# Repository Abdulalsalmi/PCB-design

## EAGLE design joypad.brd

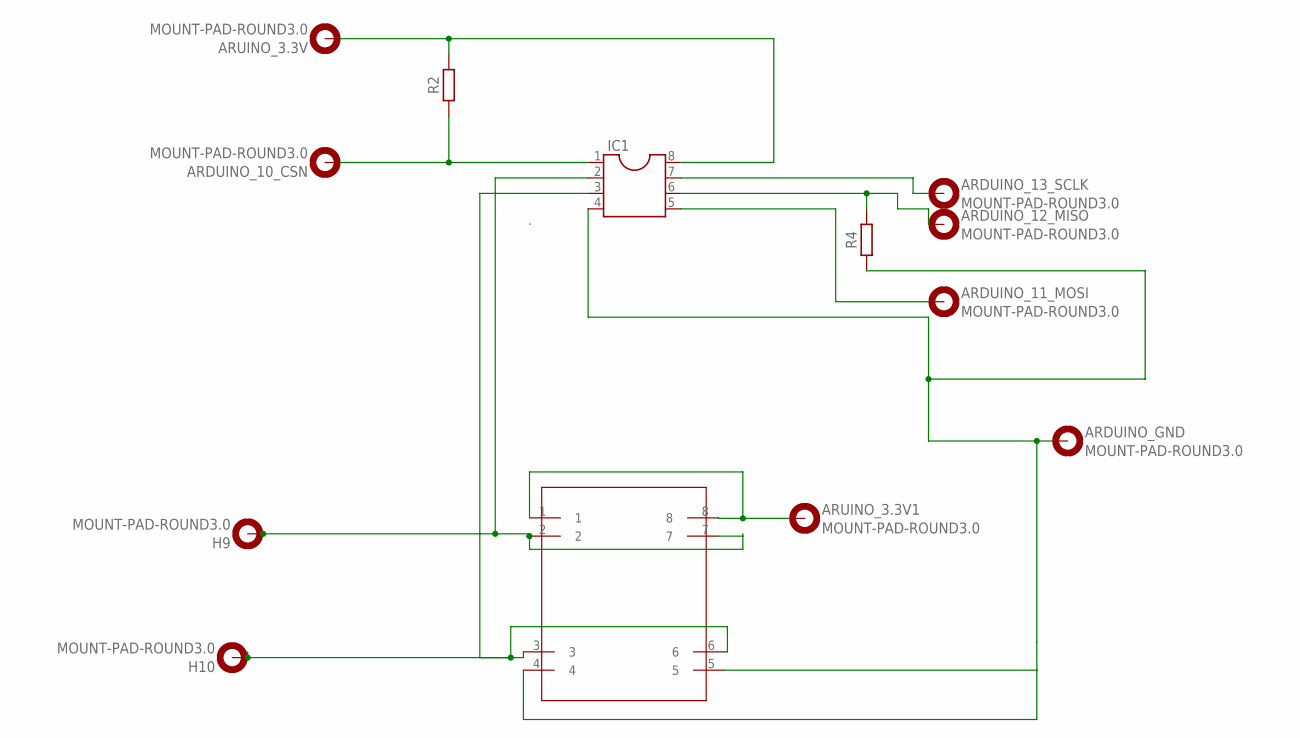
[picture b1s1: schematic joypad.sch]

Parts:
ARDUINO_10_CSN, ARDUINO_11_MOSI, ARDUINO_12_MISO, ARDUINO_13_SCLK: MOUNT-PAD-ROUND3.0; 3,0-PAD
ARDUINO_GND: MOUNT-PAD-ROUND3.0; 3,0-PAD
ARUINO_3.3V, ARUINO_3.3V1: MOUNT-PAD-ROUND3.0; 3,0-PAD
H9, H10: MOUNT-PAD-ROUND3.0; 3,0-PAD
IC1: DIL8; DIL08
R2, R4: R_AXIAL-7.2MM-PITCH; RESAD724W46L381D178B
U$1: JOYSTICK; JOYPAD

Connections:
3.3V: ARUINO_3.3V.B3,0, IC1.8, R2.2
unnamed: ARDUINO_10_CSN.B3,0, IC1.1, R2.1
unnamed: ARDUINO_13_SCLK.B3,0, IC1.7
unnamed: H10.B3,0, IC1.3, U$1.3, U$1.6
unnamed: H9.B3,0, IC1.2, U$1.2, U$1.7
unnamed: ARDUINO_12_MISO.B3,0, IC1.6, R4.2
unnamed: ARDUINO_GND.B3,0, IC1.4, R4.1, U$1.4, U$1.5
unnamed: ARDUINO_11_MOSI.B3,0, IC1.5
unnamed: ARUINO_3.3V1.B3,0, U$1.1, U$1.8

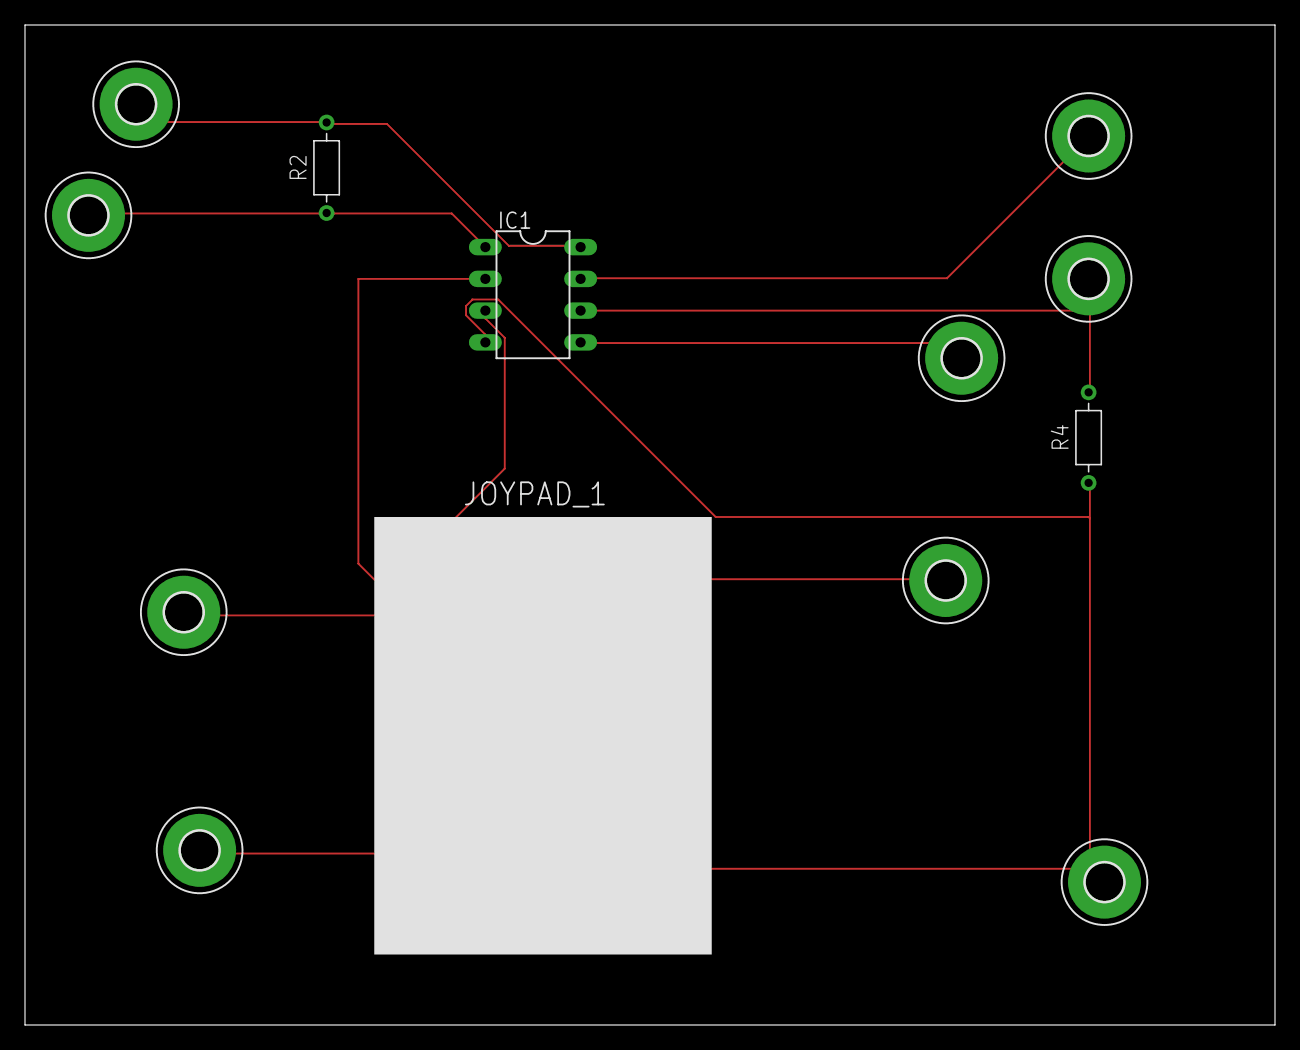
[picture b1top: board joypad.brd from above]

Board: 2 copper layers, 100.0 x 80.0 mm, 13 parts (0 on the bottom side), 9 nets.
